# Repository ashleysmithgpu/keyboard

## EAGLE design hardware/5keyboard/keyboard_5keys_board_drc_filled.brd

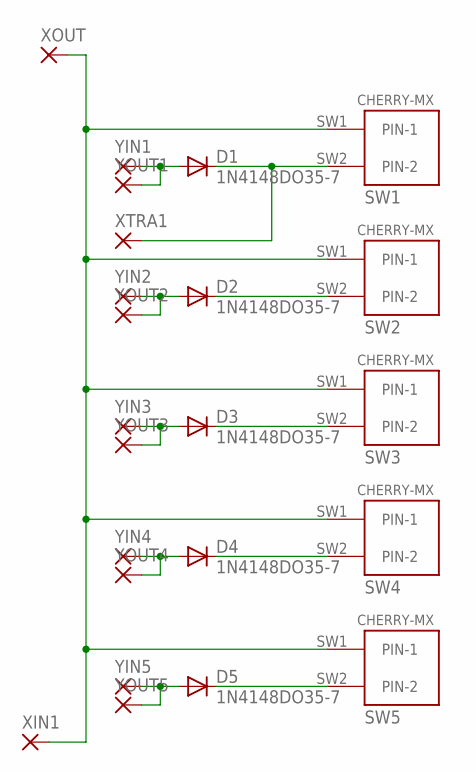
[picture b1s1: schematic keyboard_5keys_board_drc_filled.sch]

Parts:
D1, D2, D3, D4, D5: 1N4148DO35-7; DO35-7
SW1, SW2, SW3, SW4, SW5: CHERRY-MX
XIN1: 1,6/0,8
XOUT: 1,6/0,8
XTRA1: 1,6/0,8
YIN1, YIN2, YIN3, YIN4, YIN5: 1,6/0,8
YOUT1, YOUT2, YOUT3, YOUT4, YOUT5: 1,6/0,8

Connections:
unnamed: D3.A, YIN3.1, YOUT3.1
unnamed: D5.C, SW5.SW2 (PIN-2)
unnamed: D4.C, SW4.SW2 (PIN-2)
unnamed: D3.C, SW3.SW2 (PIN-2)
unnamed: D1.C, SW1.SW2 (PIN-2), XTRA1.1
unnamed: D1.A, YIN1.1, YOUT1.1
unnamed: D2.A, YIN2.1, YOUT2.1
unnamed: D2.C, SW2.SW2 (PIN-2)
unnamed: D4.A, YIN4.1, YOUT4.1
unnamed: D5.A, YIN5.1, YOUT5.1
XOUT: SW1.SW1 (PIN-1), SW2.SW1 (PIN-1), SW3.SW1 (PIN-1), SW4.SW1 (PIN-1), SW5.SW1 (PIN-1), XIN1.1, XOUT.1

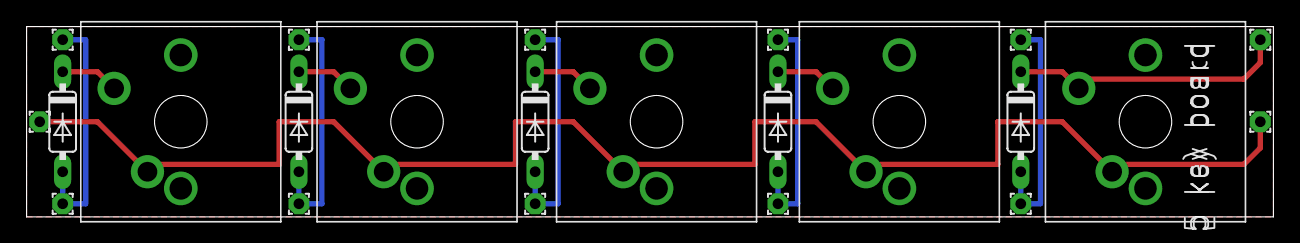
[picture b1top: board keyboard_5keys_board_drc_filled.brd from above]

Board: 2 copper layers, 95.0 x 14.5 mm, 23 parts (0 on the bottom side), 11 nets.

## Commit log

2016-04-20 first try at keyboard design
2016-04-20 changed to red for cutting colour
2016-04-21 Added design files and source files
2016-04-21 Moved text to txt file
2016-04-27 Added initial eagle files
2016-04-28 Updated distances from dimensions
2016-04-28 Moved files around, added version sent for fabrication, added module for i2c lhs
2016-04-29 Added multiplexer design
2016-10-20 - Updated keys, added i2c interface
2016-10-21 - Added i2c code, keymapping code, master/slave code
2016-10-27 - Compiling version, not tested yet
2016-10-28 - Added plate for switches
2017-09-26 New keyboard for low profile kailh
2017-10-31 Changed to using io expanders
2017-11-16 Adding low profile keyboard
2017-11-21 Added kailh switch footprint
2017-11-21 Added kailh switch pdfs
2017-11-23 Adding spaces for clicky version of kailh switch
